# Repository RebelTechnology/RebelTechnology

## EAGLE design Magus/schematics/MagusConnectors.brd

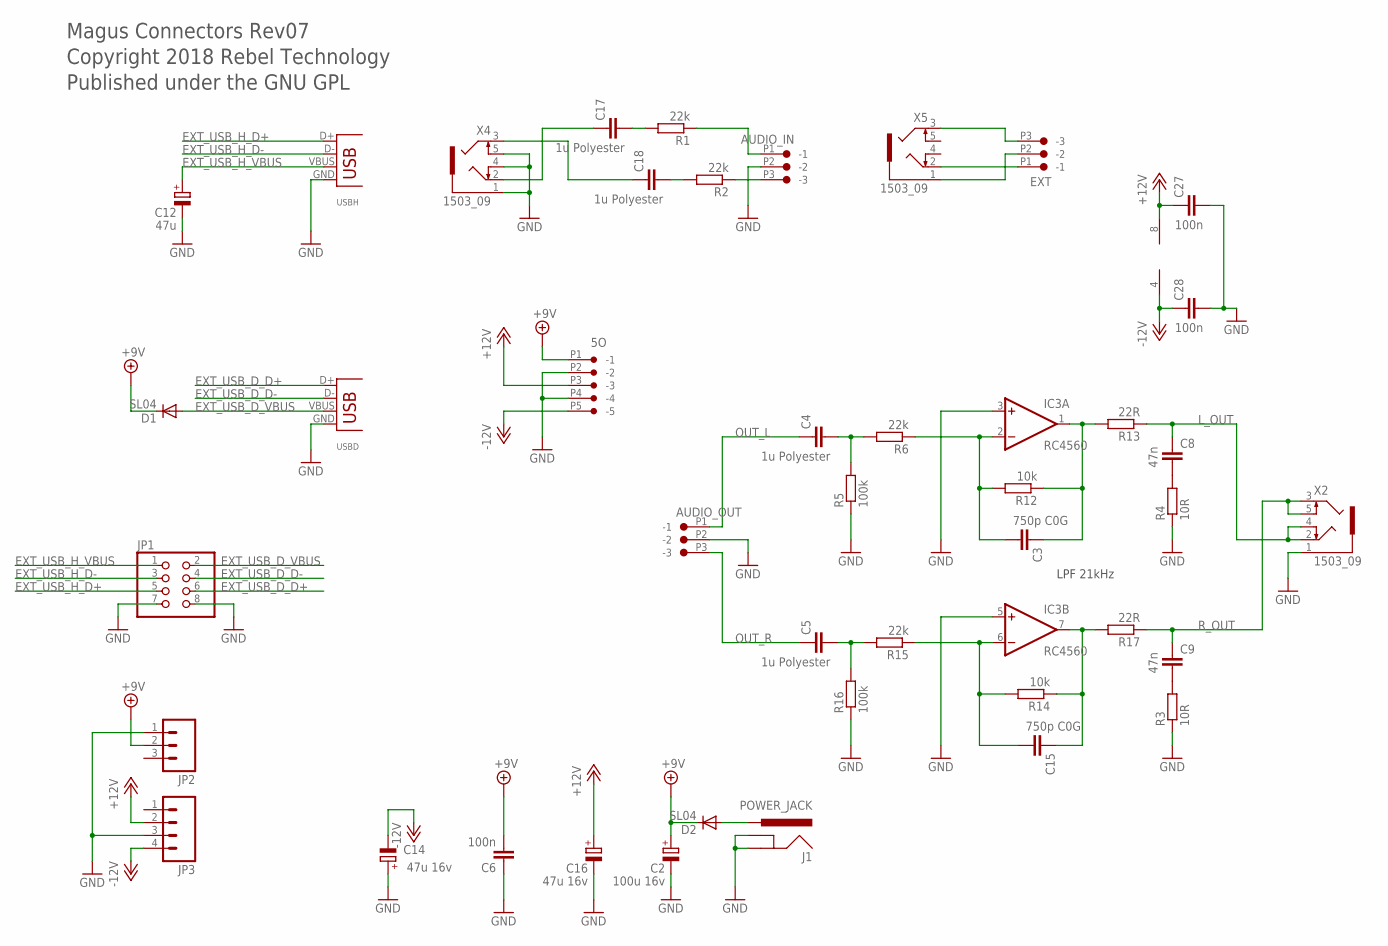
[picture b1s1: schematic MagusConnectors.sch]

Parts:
5O: CON-JST_PH_5W
AUDIO_IN: CON-JST_PH_3W
AUDIO_OUT: CON-JST_PH_3W
C2: 100u 16v; PANASONIC_D
C3, C15: 750p C0G; C0603
C4, C5, C17, C18: 1u Polyester; C1210
C6, C27, C28: 100n; C0603
C8, C9: 47n; C0603
C12: 47u; PANASONIC_B
C14, C16: 47u 16v; PANASONIC_B
D1, D2: SL04; SMA-DIODE
EXT: CON-JST_PH_3W
IC3: RC4560; SO08
J1: POWER_JACK; DC_JACK_SLOT
JP1: PINHD-2X4; 2X04
JP2: M03PTH; 1X03
JP3: M04PTH; 1X04
R1, R2, R6, R15: 22k; R0603
R3, R4: 10R; R0603
R5, R16: 100k; R0603
R12, R14: 10k; R0603
R13, R17: 22R; R0603
USBD: USB-B-H
USBH: USB-A-H
X2, X4, X5: 1503_09

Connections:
+9V: 5O.P1 (-1), C2.+, C6.2, D1.C, D2.C, JP2.2
+12V: 5O.P3 (-3), C16.+, C27.1, IC3.8 (V+), JP3.2
-12V: 5O.P5 (-5), C14.-, C28.1, IC3.4 (V-), JP3.4
EXT_USB_D_D+: JP1.6, USBD.D+
EXT_USB_D_D-: JP1.4, USBD.D-
EXT_USB_D_VBUS: D1.A, JP1.2, USBD.VBUS
EXT_USB_H_D+: JP1.5, USBH.D+
EXT_USB_H_D-: JP1.3, USBH.D-
EXT_USB_H_VBUS: C12.+, JP1.1, USBH.VBUS
GND: 5O.P2 (-2), 5O.P4 (-4), AUDIO_IN.P2 (-2), AUDIO_OUT.P2 (-2), C2.-, C6.1, C12.-, C14.+, C16.-, C27.2, C28.2, IC3.3 (+IN), IC3.5 (+IN), J1.GND, J1.GNDBREAK, JP1.7, JP1.8, JP2.1, JP3.3, R3.1, R4.1, R5.1, R16.1, USBD.GND, USBH.GND, X2.1, X4.1, X4.4, X4.5
L_OUT: C8.1, R13.1, X2.2, X2.4
unnamed: C15.2, IC3.6 (-IN), R14.2, R15.1
unnamed: C15.1, IC3.7 (OUT), R14.1, R17.2
unnamed: C3.2, IC3.2 (-IN), R6.1, R12.2
unnamed: C5.2, R15.2, R16.2
unnamed: AUDIO_IN.P3 (-3), R2.1
unnamed: AUDIO_IN.P1 (-1), R1.1
unnamed: EXT.P1 (-1), X5.2
unnamed: C4.2, R5.2, R6.2
unnamed: D2.A, J1.PWR
unnamed: C9.2, R3.2
unnamed: EXT.P3 (-3), X5.3
unnamed: EXT.P2 (-2), X5.1
unnamed: C17.2, R1.2
unnamed: C18.2, R2.2
unnamed: C3.1, IC3.1 (OUT), R12.1, R13.2
unnamed: C18.1, X4.3
unnamed: C8.2, R4.2
unnamed: C17.1, X4.2
OUT_L: AUDIO_OUT.P1 (-1), C4.1
OUT_R: AUDIO_OUT.P3 (-3), C5.1
R_OUT: C9.1, R17.1, X2.3, X2.5

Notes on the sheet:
Magus Connectors Rev07
Copyright 2018 Rebel Technology
Published under the GNU GPL
LPF 21kHz

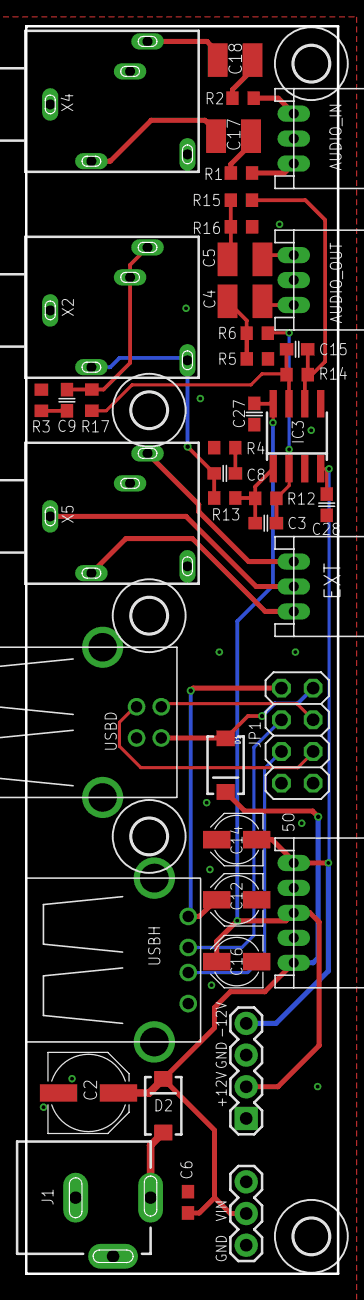
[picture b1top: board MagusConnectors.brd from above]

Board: 2 copper layers, 25.0 x 100.0 mm, 48 parts (0 on the bottom side), 32 nets.

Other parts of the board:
U$1, U$2, U$3, U$4, U$5: 2,8

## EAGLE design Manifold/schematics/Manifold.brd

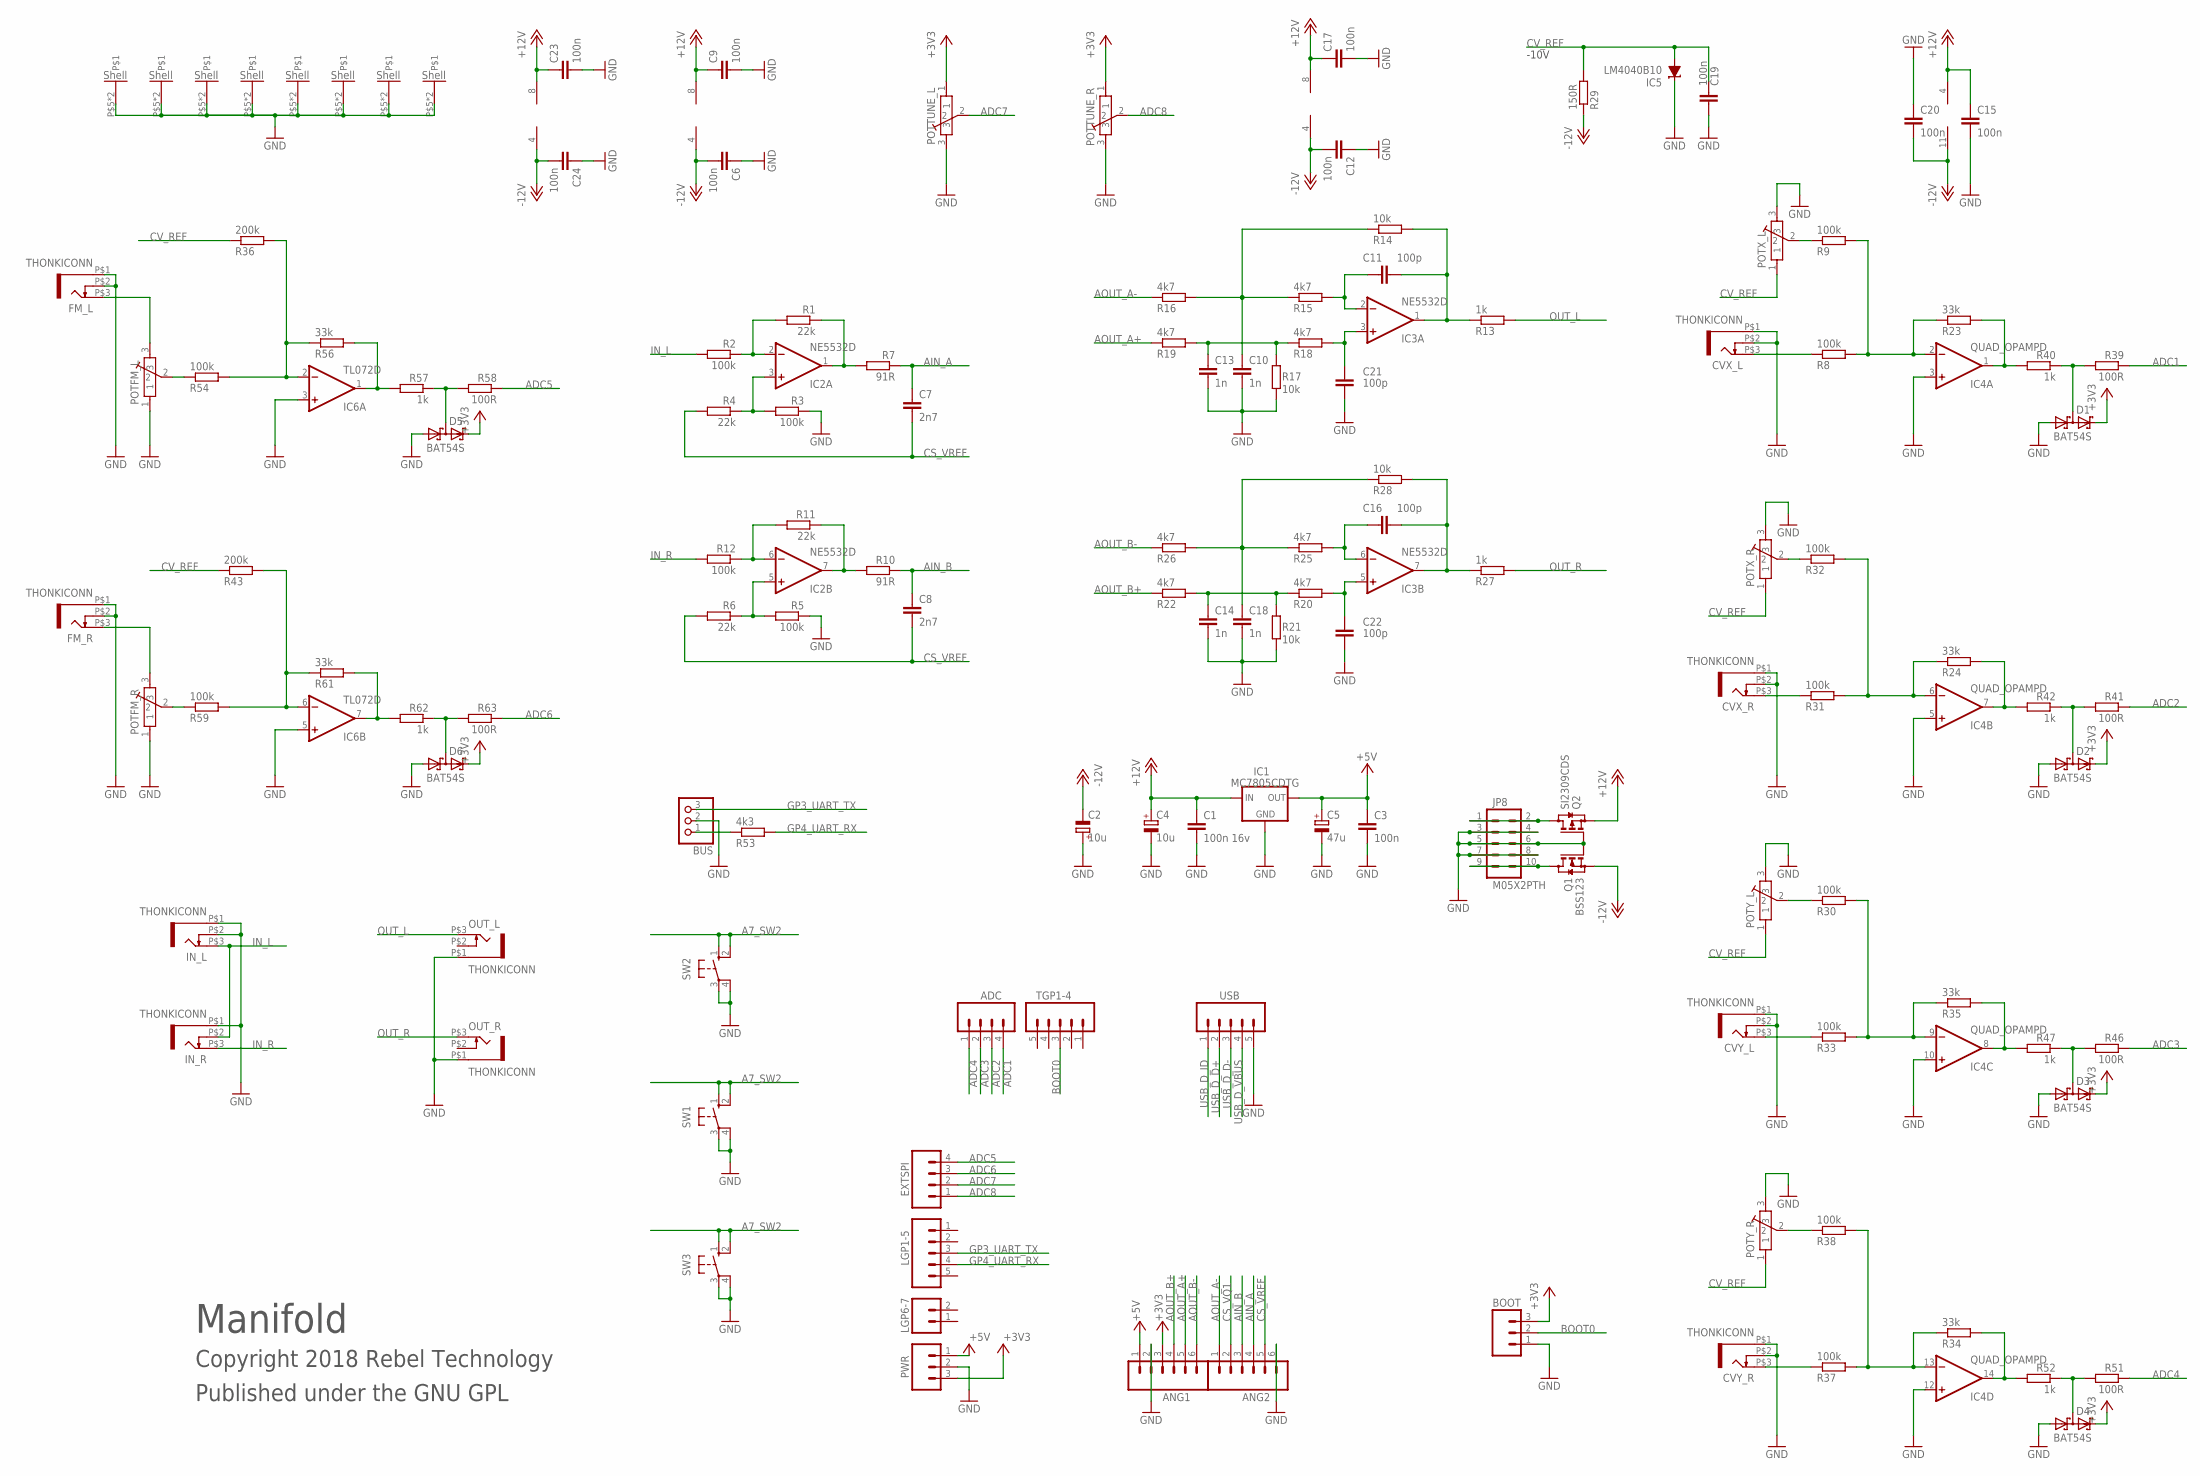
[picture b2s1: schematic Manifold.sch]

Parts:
ADC: M04PTH; 1X04
ANG1, ANG2: M06SIP; 1X06
BOOT: M03PTH; 1X03
BUS: CON-JST-1X03PH-TH; JST-B3B-PH-KL
C1: 100n 16v; C0603
C2, C4: 10u; CPOL-5
C3, C6, C9, C12, C15, C17, C19, C20, C23, C24: 100n; C0603
C5: 47u; PANASONIC_C
C7, C8: 2n7; C0603
C10, C13, C14, C18: 1n; C0603
C11, C16, C21, C22: 100p; C0603
CVX_L: THONKICONN
CVX_R: THONKICONN
CVY_L: THONKICONN
CVY_R: THONKICONN
D1, D2, D3, D4, D5, D6: BAT54S; SOT23
EXTSPI: M04PTH; 1X04
FM_L: THONKICONN
FM_R: THONKICONN
IC1: MC7805CDTG; DPACK
IC2, IC3: NE5532D; SO08
IC4: QUAD_OPAMPD; SO14
IC5: LM4040B10; DBZ_R-PDSO-G3
IC6: TL072D; SO08
IN_L: THONKICONN
IN_R: THONKICONN
JP8: M05X2PTH; AVR_ICSP
LGP1-5: M05PTH; 1X05
LGP6-7: M02PTH; 1X02
OUT_L: THONKICONN
OUT_R: THONKICONN
POTFM_L: POT-ALPS-RK09L1140
POTFM_R: POT-ALPS-RK09L1140
POTTUNE_L: POT-ALPS-RK09L1140
POTTUNE_R: POT-ALPS-RK09L1140
POTX_L: POT-ALPS-RK09L1140
POTX_R: POT-ALPS-RK09L1140
POTY_L: POT-ALPS-RK09L1140
POTY_R: POT-ALPS-RK09L1140
PWR: M03PTH; 1X03
Q1: BSS123; SOT23
Q2: SI2309CDS; SOT23
R1, R4, R6, R11: 22k; 0603
R2, R3, R5, R8, R9, R12, R30, R31, R32, R33, R37, R38, R54, R59: 100k; 0603
R7, R10: 91R; 0603
R13, R27, R40, R42, R47, R52, R57, R62: 1k; 0603
R14, R17, R21, R28: 10k; 0603
R15, R16, R18, R19, R20, R22, R25, R26: 4k7; 0603
R23, R24, R34, R35, R56, R61: 33k; 0603
R29: 150R; 0603
R36, R43: 200k; 0603
R39, R41, R46, R51, R58, R63: 100R; 0603
R53: 4k3; 0603
SW1, SW2, SW3: 10-XX; B3F-10XX
TGP1-4: M05PTH; 1X05
USB: M05PTH; 1X05

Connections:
+3V3: ANG1.3, BOOT.3, D1.2 (C2), D2.2 (C2), D3.2 (C2), D4.2 (C2), D5.2 (C2), D6.2 (C2), POTTUNE_L.1, POTTUNE_R.1, PWR.3
+5V: ANG1.1, C3.1, C5.+, IC1.3 (OUT), PWR.1
+12V: C1.1, C4.+, C9.1, C15.1, C17.1, C23.1, IC1.1 (IN), IC2.8 (V+), IC3.8 (V+), IC4.4 (V+), IC6.8 (V+), Q2.2 (S)
-12V: C2.-, C6.2, C12.2, C20.2, C24.2, IC2.4 (V-), IC3.4 (V-), IC4.11 (V-), IC6.4 (V-), Q1.2 (S), R29.1
A7_SW2: SW1.1 (S), SW1.2 (S1), SW2.1 (S), SW2.2 (S1), SW3.1 (S), SW3.2 (S1)
ADC1: ADC.4, R39.1
ADC2: ADC.3, R41.1
ADC3: ADC.2, R46.1
ADC4: ADC.1, R51.1
ADC5: EXTSPI.4, R58.1
ADC6: EXTSPI.3, R63.1
ADC7: EXTSPI.2, POTTUNE_L.2
ADC8: EXTSPI.1, POTTUNE_R.2
AIN_A: ANG2.4, C7.1, R7.1
AIN_B: ANG2.3, C8.1, R10.1
AOUT_A+: ANG1.5, R19.1
AOUT_A-: ANG2.1, R16.1
AOUT_B+: ANG1.4, R22.1
AOUT_B-: ANG1.6, R26.1
BOOT0: BOOT.2, TGP1-4.3
CS_VQ1: ANG2.2
CS_VREF: ANG2.5, C7.2, C8.2, R4.2, R6.2
CV_REF: C19.1, IC5.2 (A), POTX_L.1, POTX_R.1, POTY_L.1, POTY_R.1, R29.2, R36.1, R43.1
EXT_UART_RX: BUS.1, R53.1
GND: ANG1.2, ANG2.6, BOOT.1, BUS.2, C1.2, C2.+, C3.2, C4.-, C5.-, C6.1, C9.2, C10.2, C12.1, C13.2, C14.2, C15.2, C17.2, C18.2, C19.2, C20.1, C21.2, C22.2, C23.2, C24.1, CVX_L.P$1 (5), CVX_L.P$2 (4), CVX_R.P$1 (5), CVX_R.P$2 (4), CVY_L.P$1 (5), CVY_L.P$2 (4), CVY_R.P$1 (5), CVY_R.P$2 (4), D1.1 (A1), D2.1 (A1), D3.1 (A1), D4.1 (A1), D5.1 (A1), D6.1 (A1), FM_L.P$1 (5), FM_L.P$2 (4), FM_R.P$1 (5), FM_R.P$2 (4), IC1.4 (GND), IC4.3 (+IN), IC4.5 (+IN), IC4.10 (+IN), IC4.12 (+IN), IC5.1 (C), IC6.3 (+IN), IC6.5 (+IN), IN_L.P$1 (5), IN_L.P$2 (4), IN_R.P$1 (5), JP8.3, JP8.4, JP8.5, JP8.6, JP8.7, JP8.8, OUT_L.P$1 (5), OUT_R.P$1 (5), POTFM_L.1, POTFM_L.P$5, POTFM_L.P$6, POTFM_R.1, POTFM_R.P$5, POTFM_R.P$6, POTTUNE_L.3, POTTUNE_L.P$5, POTTUNE_L.P$6, POTTUNE_R.3, POTTUNE_R.P$5, POTTUNE_R.P$6, POTX_L.3, POTX_L.P$5, POTX_L.P$6, POTX_R.3, POTX_R.P$5, POTX_R.P$6, POTY_L.3, POTY_L.P$5, POTY_L.P$6, POTY_R.3, POTY_R.P$5, POTY_R.P$6, PWR.2, Q1.1 (G), Q2.1 (G), R3.1, R5.1, R17.1, R21.1, SW1.3, SW1.4 (P1), SW2.3, SW2.4 (P1), SW3.3, SW3.4 (P1), USB.5
GP3_UART_TX: BUS.3, LGP1-5.3
GP4_UART_RX: LGP1-5.4, R53.2
IN_L: IN_L.P$3 (3), IN_R.P$2 (4), R2.2
IN_R: IN_R.P$3 (3), R12.2
unnamed: IC2.1 (OUT), R1.1, R7.2
unnamed: IC2.3 (+IN), R3.2, R4.1
unnamed: CVX_L.P$3 (3), R8.1
unnamed: IC2.5 (+IN), R5.2, R6.1
unnamed: IC2.6 (-IN), R11.2, R12.1
unnamed: IC4.9 (-IN), R30.2, R33.2, R35.1
unnamed: C11.1, IC3.2 (-IN), R15.2
unnamed: JP8.9, JP8.10, Q1.3 (D)
unnamed: IC2.2 (-IN), R1.2, R2.1
unnamed: IC2.7 (OUT), R10.2, R11.1
unnamed: C21.1, IC3.3 (+IN), R18.2
unnamed: JP8.1, JP8.2, Q2.3 (D)
unnamed: IC4.2 (-IN), R8.2, R9.2, R23.1
unnamed: POTX_L.2, R9.1
unnamed: C13.1, R17.2, R18.1, R19.2
unnamed: D1.3 (C1A2), R39.2, R40.1
unnamed: IC4.1 (OUT), R23.2, R40.2
unnamed: C16.2, IC3.7 (OUT), R27.1, R28.2
unnamed: CVX_R.P$3 (3), R31.1
unnamed: IC4.6 (-IN), R24.1, R31.2, R32.2
unnamed: POTX_R.2, R32.1
unnamed: IC4.7 (OUT), R24.2, R42.2
unnamed: D2.3 (C1A2), R41.2, R42.1
unnamed: C18.1, R25.1, R26.2, R28.1
unnamed: CVY_L.P$3 (3), R33.1
unnamed: C16.1, IC3.6 (-IN), R25.2
unnamed: POTY_L.2, R30.1
unnamed: IC4.8 (OUT), R35.2, R47.2
unnamed: D3.3 (C1A2), R46.2, R47.1
unnamed: C22.1, IC3.5 (+IN), R20.2
unnamed: CVY_R.P$3 (3), R37.1
unnamed: C14.1, R20.1, R21.2, R22.2
unnamed: IC4.13 (-IN), R34.1, R37.2, R38.2
unnamed: POTY_R.2, R38.1
unnamed: IC4.14 (OUT), R34.2, R52.2
unnamed: D4.3 (C1A2), R51.2, R52.1
unnamed: C11.2, IC3.1 (OUT), R13.1, R14.2
unnamed: C10.1, R14.1, R15.1, R16.2
unnamed: POTFM_L.2, R54.1
unnamed: IC6.1 (OUT), R56.2, R57.2
unnamed: D5.3 (C1A2), R57.1, R58.2
unnamed: POTFM_R.2, R59.1
unnamed: IC6.6 (-IN), R43.2, R59.2, R61.1
unnamed: FM_R.P$3 (3), POTFM_R.3
unnamed: IC6.7 (OUT), R61.2, R62.2
unnamed: D6.3 (C1A2), R62.1, R63.2
unnamed: IC6.2 (-IN), R36.2, R54.2, R56.1
unnamed: FM_L.P$3 (3), POTFM_L.3
OUT_L: OUT_L.P$3 (3), R13.2
OUT_R: OUT_R.P$3 (3), R27.2
USB_D_D+: USB.2
USB_D_D-: USB.3
USB_D_ID: USB.1
USB_D_VBUS: USB.4

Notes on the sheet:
Manifold
Copyright 2018 Rebel Technology
Published under the GNU GPL
-10V

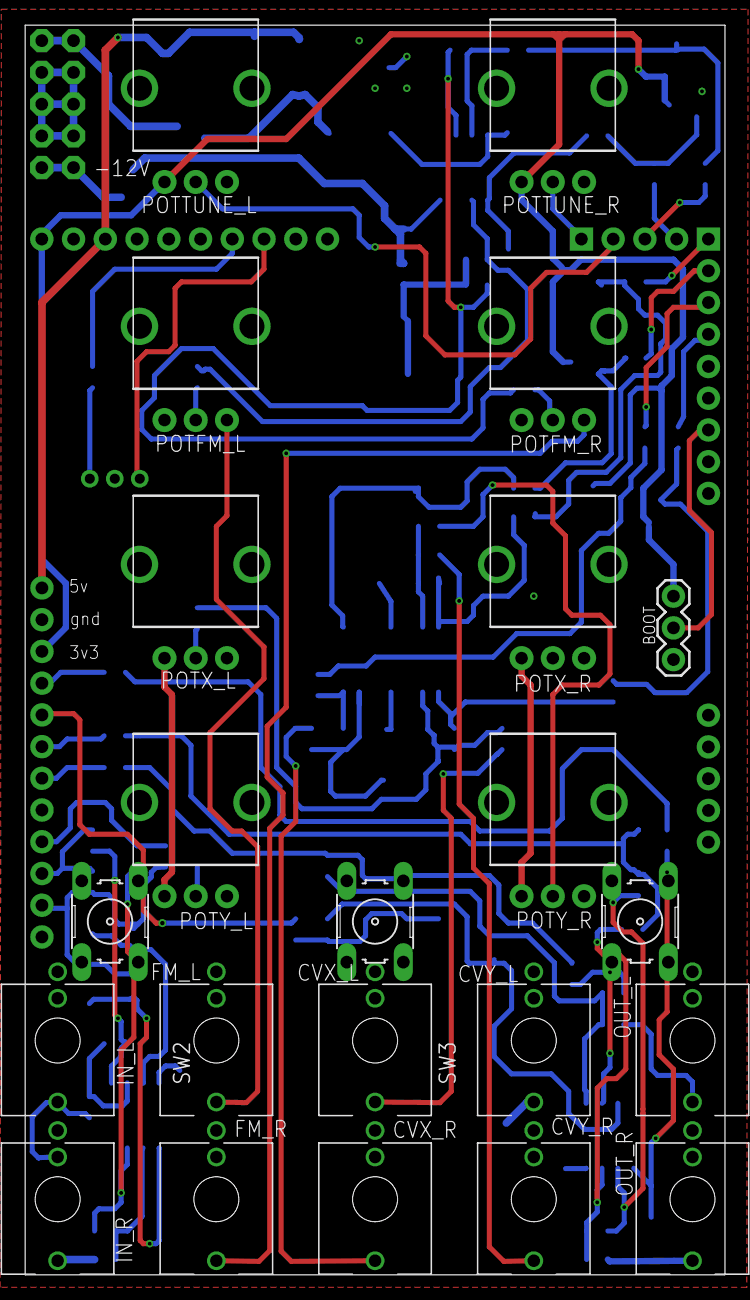
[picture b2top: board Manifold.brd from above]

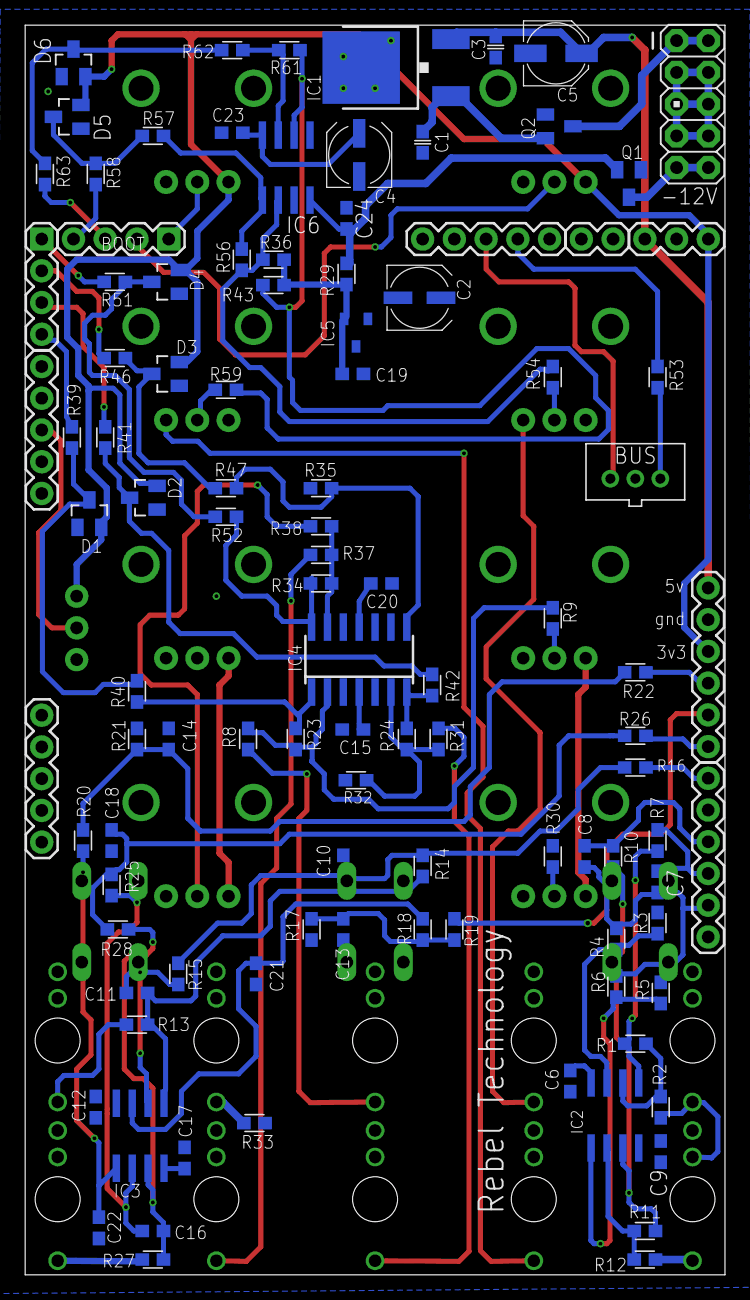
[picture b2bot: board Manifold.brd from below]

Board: 2 copper layers, 56.0 x 100.0 mm, 127 parts (105 on the bottom side), 78 nets.

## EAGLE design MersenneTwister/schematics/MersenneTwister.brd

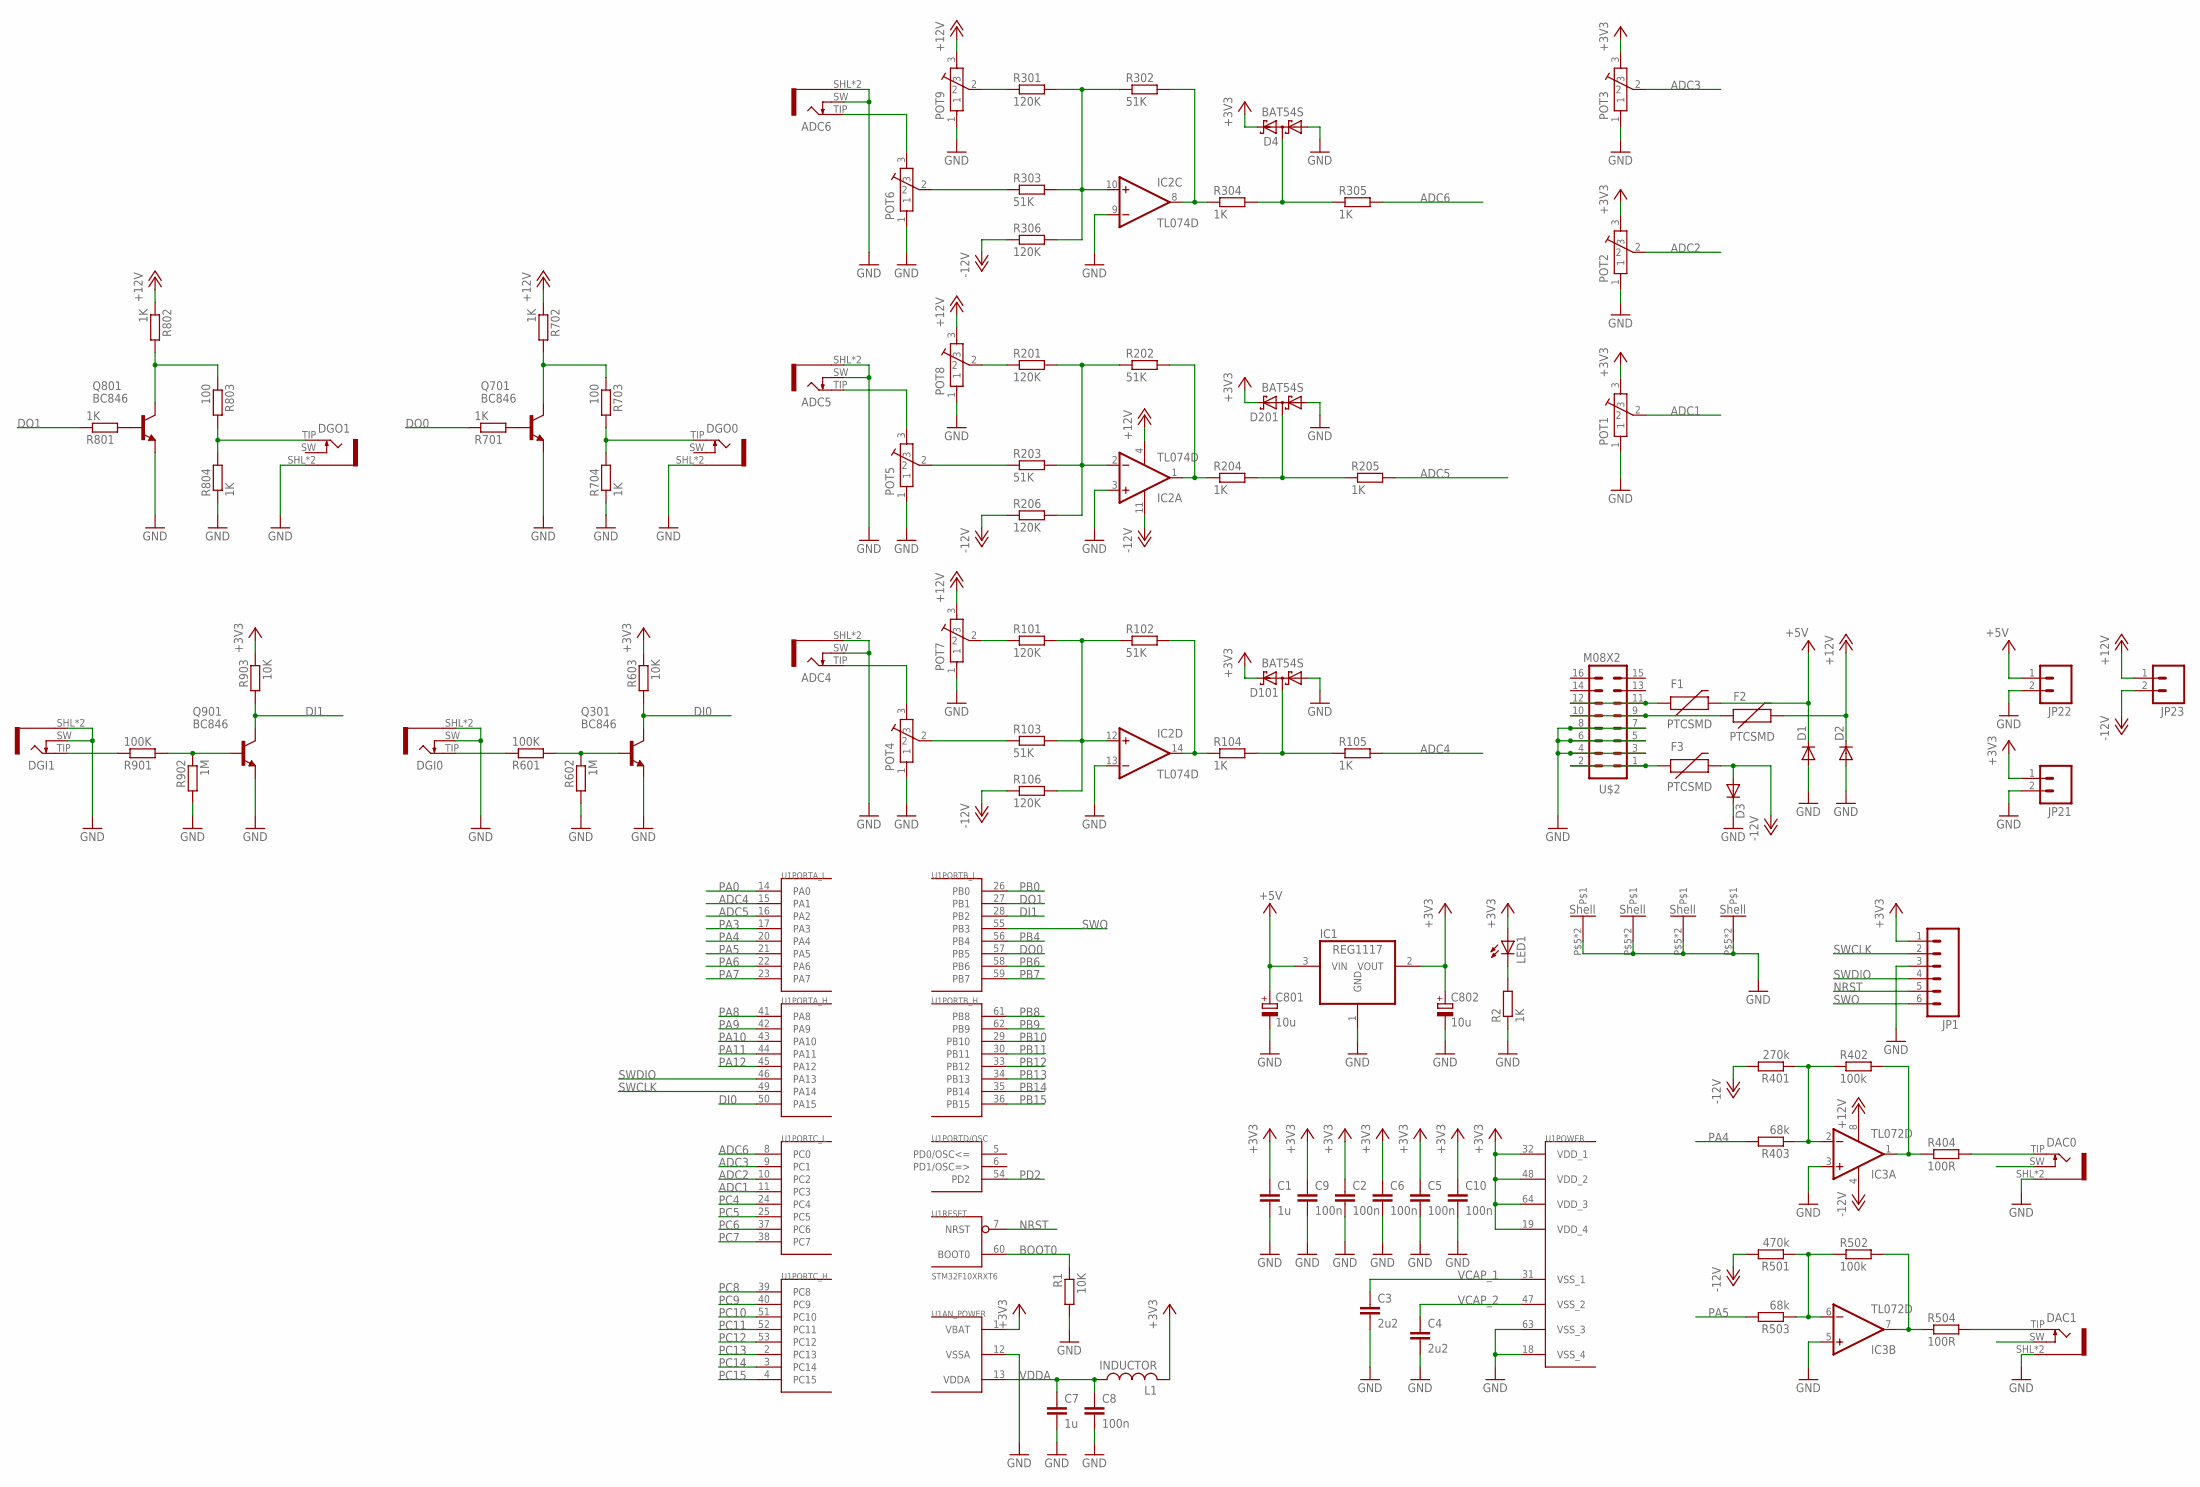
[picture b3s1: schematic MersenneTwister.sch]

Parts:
ADC4, ADC5, ADC6: JACK-PJ-301B; PJ-301B
C1, C7: 1u; C0603
C2, C5, C6, C8, C9, C10: 100n; C0603
C3, C4: 2u2; C0603
C801, C802: 10u; PANASONIC_A
D1, D2, D3: DIODESMA; SMA-DIODE
D4, D101, D201: BAT54S; SOT23
DAC0, DAC1: JACK-PJ-301B; PJ-301B
DGI0, DGI1: JACK-PJ-301B; PJ-301B
DGO0, DGO1: JACK-PJ-301B; PJ-301B
F1, F2, F3: PTCSMD; PTC-1206
IC1: REG1117; SOT223
IC2: TL074D; SO14
IC3: TL072D; SO08
JP1: M06SIP; 1X06
JP21, JP22, JP23: M02PTH; 1X02
L1: INDUCTOR; 0603
LED1: LEDCHIPLED_0603; CHIPLED_0603
POT1, POT2, POT3, POT4, POT5, POT6, POT7, POT8, POT9: POT-ALPS-RK09L1140
Q301, Q701, Q801, Q901: BC846; SOT23
R1, R603, R903: 10K; R0603
R2, R104, R105, R204, R205, R304, R305, R701, R702, R704, R801, R802, R804: 1K; R0603
R101, R106, R201, R206, R301, R306: 120K; R0603
R102, R103, R202, R203, R302, R303: 51K; R0603
R401: 270k; R0603
R402, R502: 100k; R0603
R403, R503: 68k; R0603
R404, R504: 100R; R0603
R501: 470k; R0603
R601, R901: 100K; R0603
R602, R902: 1M; R0603
R703, R803: 100; R0603
U1: STM32F10XRXT6; TQFP64
U$2: M08X2; 2X8

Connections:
+3V3: C1.1, C2.1, C5.1, C6.1, C9.1, C10.1, C802.+, D4.2 (C2), D101.2 (C2), D201.2 (C2), IC1.2 (VOUT), JP1.1, JP21.1, L1.2, LED1.A, POT1.3, POT2.3, POT3.3, R603.1, R903.1, U1.1 (VBAT), U1.19 (VDD_4), U1.32 (VDD_1), U1.48 (VDD_2), U1.64 (VDD_3)
+5V: C801.+, D1.C, F1.2, IC1.3 (VIN), JP22.1
+12V: D2.C, F2.2, IC2.4 (V+), IC3.8 (V+), JP23.1, POT7.3, POT8.3, POT9.3, R702.1, R802.1
-12V: D3.A, F3.2, IC2.11 (V-), IC3.4 (V-), JP23.2, R106.1, R206.1, R306.1, R401.2, R501.2
ADC1: POT1.2, U1.11 (PC3)
ADC2: POT2.2, U1.10 (PC2)
ADC3: POT3.2, U1.9 (PC1)
ADC4: R105.2, U1.15 (PA1)
ADC5: R205.2, U1.16 (PA2)
ADC6: R305.2, U1.8 (PC0)
BOOT0: R1.1, U1.60 (BOOT0)
DI0: Q301.3 (C), R603.2, U1.50 (PA15)
DI1: Q901.3 (C), R903.2, U1.28 (PB2)
DO0: R701.1, U1.57 (PB5)
DO1: R801.1, U1.27 (PB1)
GND: ADC4.SHL (SLEEVE), ADC4.SLV (SLEEVE), ADC4.SW, ADC5.SHL (SLEEVE), ADC5.SLV (SLEEVE), ADC5.SW, ADC6.SHL (SLEEVE), ADC6.SLV (SLEEVE), ADC6.SW, C1.2, C2.2, C3.2, C4.2, C5.2, C6.2, C7.2, C8.2, C9.2, C10.2, C801.-, C802.-, D1.A, D2.A, D3.C, D4.1 (A1), D101.1 (A1), D201.1 (A1), DAC0.SHL (SLEEVE), DAC0.SLV (SLEEVE), DAC1.SHL (SLEEVE), DAC1.SLV (SLEEVE), DGI0.SHL (SLEEVE), DGI0.SLV (SLEEVE), DGI0.SW, DGI1.SHL (SLEEVE), DGI1.SLV (SLEEVE), DGI1.SW, DGO0.SHL (SLEEVE), DGO0.SLV (SLEEVE), DGO1.SHL (SLEEVE), DGO1.SLV (SLEEVE), IC1.1 (GND), IC2.3 (+IN), IC2.9 (-IN), IC2.13 (-IN), IC3.3 (+IN), IC3.5 (+IN), JP1.3, JP21.2, JP22.2, POT1.1, POT1.P$5, POT1.P$6, POT2.1, POT2.P$5, POT2.P$6, POT3.1, POT4.1, POT5.1, POT6.1, POT7.1, POT7.P$5, POT7.P$6, POT8.1, POT8.P$5, POT8.P$6, POT9.1, Q301.2 (E), Q701.2 (E), Q801.2 (E), Q901.2 (E), R1.2, R2.1, R602.2, R704.1, R804.1, R902.2, U1.12 (VSSA), U1.18 (VSS_4), U1.63 (VSS_3), U$2.3, U$2.4, U$2.5, U$2.6, U$2.7, U$2.8
unnamed: ADC6.TIP, POT6.3
unnamed: IC2.12 (+IN), R101.2, R102.1, R103.2, R106.2
unnamed: POT7.2, R101.1
unnamed: IC2.14 (OUT), R102.2, R104.1
unnamed: IC3.7 (OUT), R502.2, R504.1
unnamed: F3.1, U$2.1, U$2.2
unnamed: IC3.1 (OUT), R402.2, R404.1
unnamed: IC2.10 (+IN), R301.2, R302.1, R303.2, R306.2
unnamed: Q901.1 (B), R901.2, R902.1
unnamed: Q801.1 (B), R801.2
unnamed: D201.3 (C1A2), R204.2, R205.1
unnamed: IC3.2 (-IN), R401.1, R402.1, R403.1
unnamed: IC2.2 (-IN), R201.2, R202.1, R203.2, R206.2
unnamed: POT8.2, R201.1
unnamed: IC2.1 (OUT), R202.2, R204.1
unnamed: ADC5.TIP, POT5.3
unnamed: IC3.6 (-IN), R501.1, R502.1, R503.1
unnamed: LED1.C, R2.2
unnamed: D101.3 (C1A2), R104.2, R105.1
unnamed: DGI1.TIP, R901.1
unnamed: DGO1.TIP, R803.2, R804.2
unnamed: DGI0.TIP, R601.1
unnamed: Q801.3 (C), R802.2, R803.1
unnamed: POT5.2, R203.1
unnamed: Q301.1 (B), R601.2, R602.1
unnamed: POT9.2, R301.1
unnamed: DAC0.TIP, R404.2
unnamed: DAC1.TIP, R504.2
unnamed: IC2.8 (OUT), R302.2, R304.1
unnamed: Q701.1 (B), R701.2
unnamed: DGO0.TIP, R703.2, R704.2
unnamed: POT6.2, R303.1
unnamed: D4.3 (C1A2), R304.2, R305.1
unnamed: Q701.3 (C), R702.2, R703.1
unnamed: ADC4.TIP, POT4.3
unnamed: POT4.2, R103.1
unnamed: F1.1, U$2.11, U$2.12
unnamed: F2.1, U$2.9, U$2.10
NRST: JP1.5, U1.7 (NRST)
PA0: U1.14 (PA0)
PA3: U1.17 (PA3)
PA4: R403.2, U1.20 (PA4)
PA5: R503.2, U1.21 (PA5)
PA6: U1.22 (PA6)
PA7: U1.23 (PA7)
PA8: U1.41 (PA8)
PA9: U1.42 (PA9)
PA10: U1.43 (PA10)
PA11: U1.44 (PA11)
PA12: U1.45 (PA12)
PB0: U1.26 (PB0)
PB4: U1.56 (PB4)
PB6: U1.58 (PB6)
PB7: U1.59 (PB7)
PB8: U1.61 (PB8)
PB9: U1.62 (PB9)
PB10: U1.29 (PB10)
PB11: U1.30 (PB11)
PB12: U1.33 (PB12)
PB13: U1.34 (PB13)
PB14: U1.35 (PB14)
PB15: U1.36 (PB15)
PC4: U1.24 (PC4)
PC5: U1.25 (PC5)
PC6: U1.37 (PC6)
PC7: U1.38 (PC7)
PC8: U1.39 (PC8)
PC9: U1.40 (PC9)
PC10: U1.51 (PC10)
PC11: U1.52 (PC11)
PC12: U1.53 (PC12)
PC13: U1.2 (PC13)
PC14: U1.3 (PC14)
PC15: U1.4 (PC15)
PD2: U1.54 (PD2)
SWCLK: JP1.2, U1.49 (PA14)
SWDIO: JP1.4, U1.46 (PA13)
SWO: JP1.6, U1.55 (PB3)
VCAP_1: C3.1, U1.31 (VSS_1)
VCAP_2: C4.1, U1.47 (VSS_2)
VDDA: C7.1, C8.1, L1.1, U1.13 (VDDA)

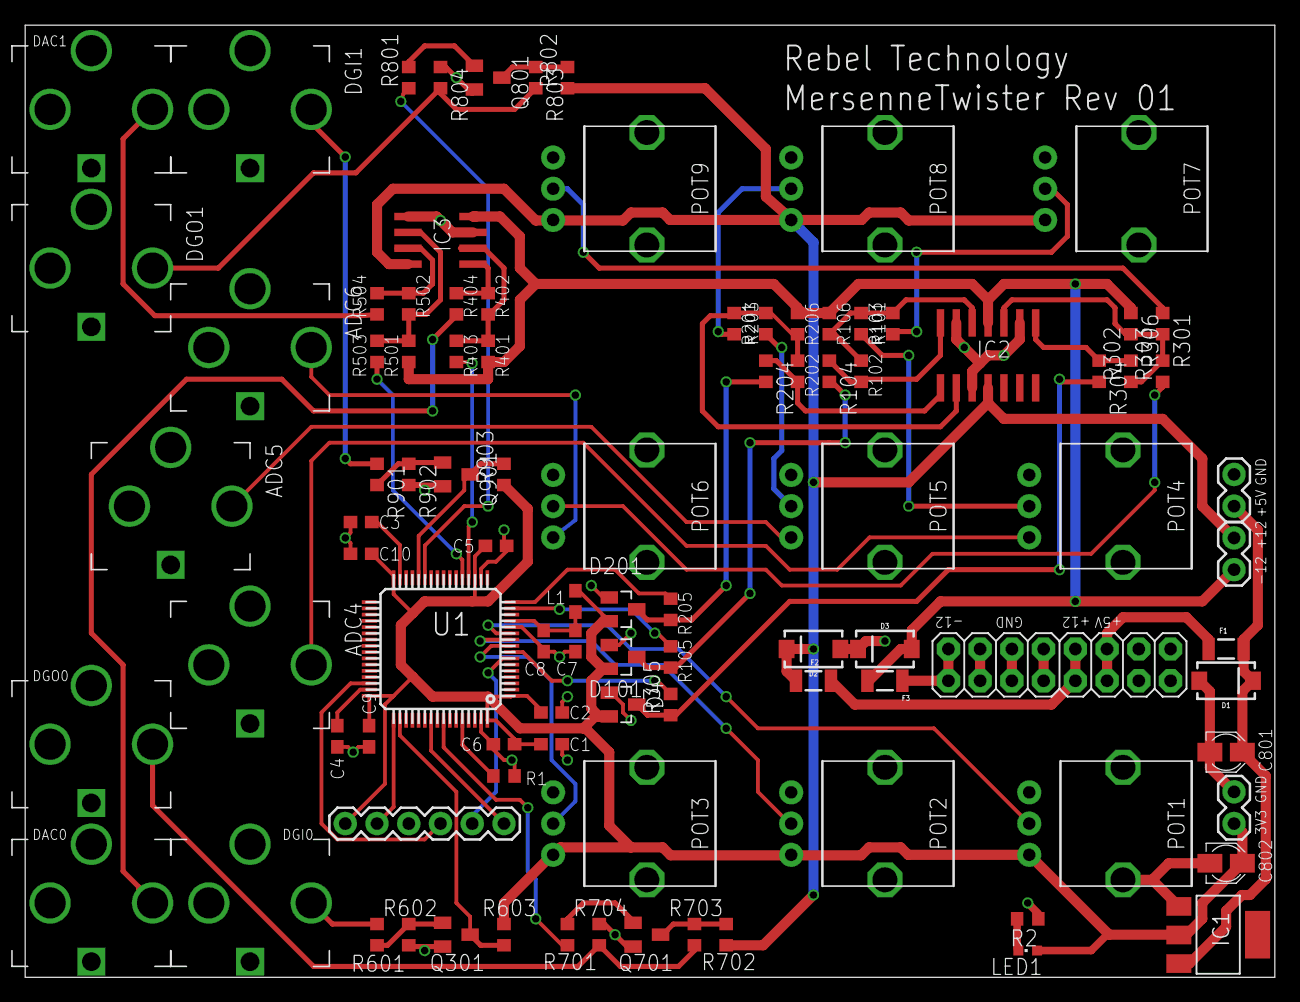
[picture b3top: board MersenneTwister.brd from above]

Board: 2 copper layers, 100.0 x 76.2 mm, 97 parts (0 on the bottom side), 63 nets.

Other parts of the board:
U$3: RT-LOGO-35MM-BL

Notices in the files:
parts and their libraries:
SparkFun: Licensing: CC v3.0 Share-Alike You are welcome to use this library for commercial purposes.
SparkFun-Connectors: Licensing: Creative Commons ShareAlike 4.0 International - https://creativecommons.org/licenses/by-sa/4.0
Wurth-connectors: Copyright: Würth Elektronik
